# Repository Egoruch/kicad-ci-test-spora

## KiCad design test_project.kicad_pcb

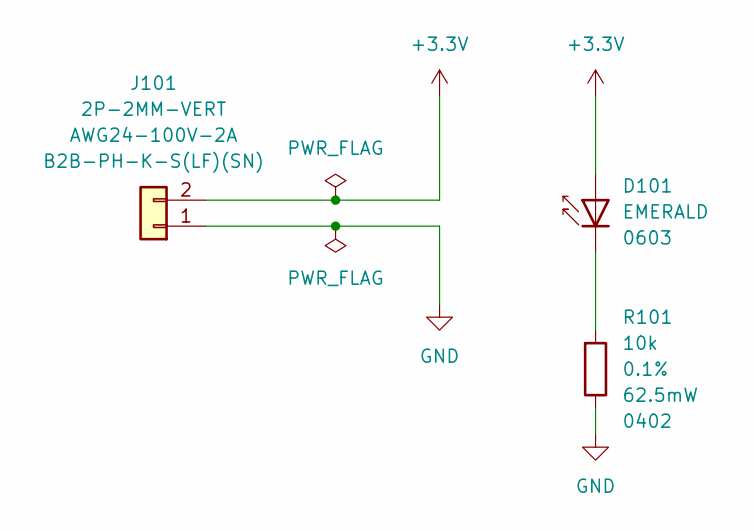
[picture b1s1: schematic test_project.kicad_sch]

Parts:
D101: EMERALD; LED_0603_E_1608Metric; Manufacturer Part Number 19-217/GHC-YR1S2/3T; LCSC Part Number C72043
J101: 2P-2MM-VERT; JST_PH_B2B-PH-K_1x02_P2.00mm_Vertical; Manufacturer Part Number B2B-PH-K-S(LF)(SN); LCSC Part Number C131337
R101: 10k; R_0402_1005Metric; Tolerance 0.1%; Manufacturer Part Number RT0402BRD0710KL; LCSC Part Number C190095

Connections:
+3.3V: D101.2 (A), J101.2
GND: J101.1, R101.2
unnamed: D101.1 (K), R101.1

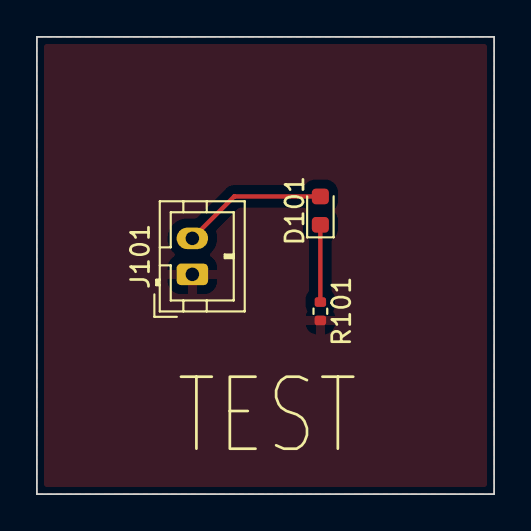
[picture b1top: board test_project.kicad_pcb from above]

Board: 4 copper layers, 25.4 x 25.4 mm, 3 parts (0 on the bottom side), 3 nets.

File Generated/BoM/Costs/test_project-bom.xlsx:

|  | KiBot Bill of Materials
 |  | Schematic: | test_project | Component Groups: | 3
 |  | Variant: | default | Component Count: | 3 (2 SMD/ 1 THT)
 |  | Revision: |  | Fitted Components: | 3 (2 SMD/ 1 THT)
 |  | Date: | 2024-01-10_16-35-41 | Number of PCBs: | 1
 |  | KiCad Version: | 7.0.9-7.0.9~ubuntu23.04.1 | Total Components: | 3
Row | Description | Part | Part Lib | References | Value | Footprint | Footprint Lib | Quantity Per PCB | Build Quantity | Status | Datasheet | Sheetpath | Source BoM | Reference | Package | Manufacturer Part Number | LCSC Part Number | Supplier 1 | Supplier Part Number 1 | Lifecycle | Assembly | Tolerance | Power | Wire | JLCPCB Rotation Offset
1 | Colorless transparence -40℃~+85℃ 520nm~535nm Emerald 120° 110mW 0603 Light Emit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 | 19-217/GHC-YR1S2/3T | Library | D101 | EMERALD | LED_0603_E_1608Metric | LED_SMD | 1 | 1 |  | https://jlcpcb.com/partdetail/EverlightElec-19_217_GHC_YR1S2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 | / | test_project(1) |  | 0603 | 19-217/GHC-YR1S2/3T | C72043 |  |  | ✅ Production
2 | 1x2P PH 1 2mm 2 Brass Straight,P=2mm Wire To Board / Wire To Wire Connector ROHS | B2B-PH-K-S(LF)(SN) | Library | J101 | 2P-2MM-VERT | JST_PH_B2B-PH-K_1x02_P2.00mm_Vertical | Connector_JST | 1 | 1 |  | https://jlcpcb.com/partdetail/Jst_SalesAmerica-B2B_PH_K_S_LF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 | / | test_project(1) |  | Straight,P=2mm | B2B-PH-K-S(LF)(SN) | C131337 |  |  | ✅ Production |  |  |  | AWG24-100V-2A | 180
3 | 62.5mW Thin Film Resistor ±25ppm/℃ ±0.1% 10kΩ 0402 Chip Resistor - Surface Moun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 | RT0402BRD0710KL | Library | R101 | 10k 0.1% 62.5mW | R_0402_1005Metric | Resistor_SMD | 1 | 1 |  | https://jlcpcb.com/partdetail/Yageo-RT0402BRD0710KL/C190095 | / | test_project(1) |  | 0402 | RT0402BRD0710KL | C190095 |  |  | 🔵 Prototype |  | 0.1% | 62.5mW

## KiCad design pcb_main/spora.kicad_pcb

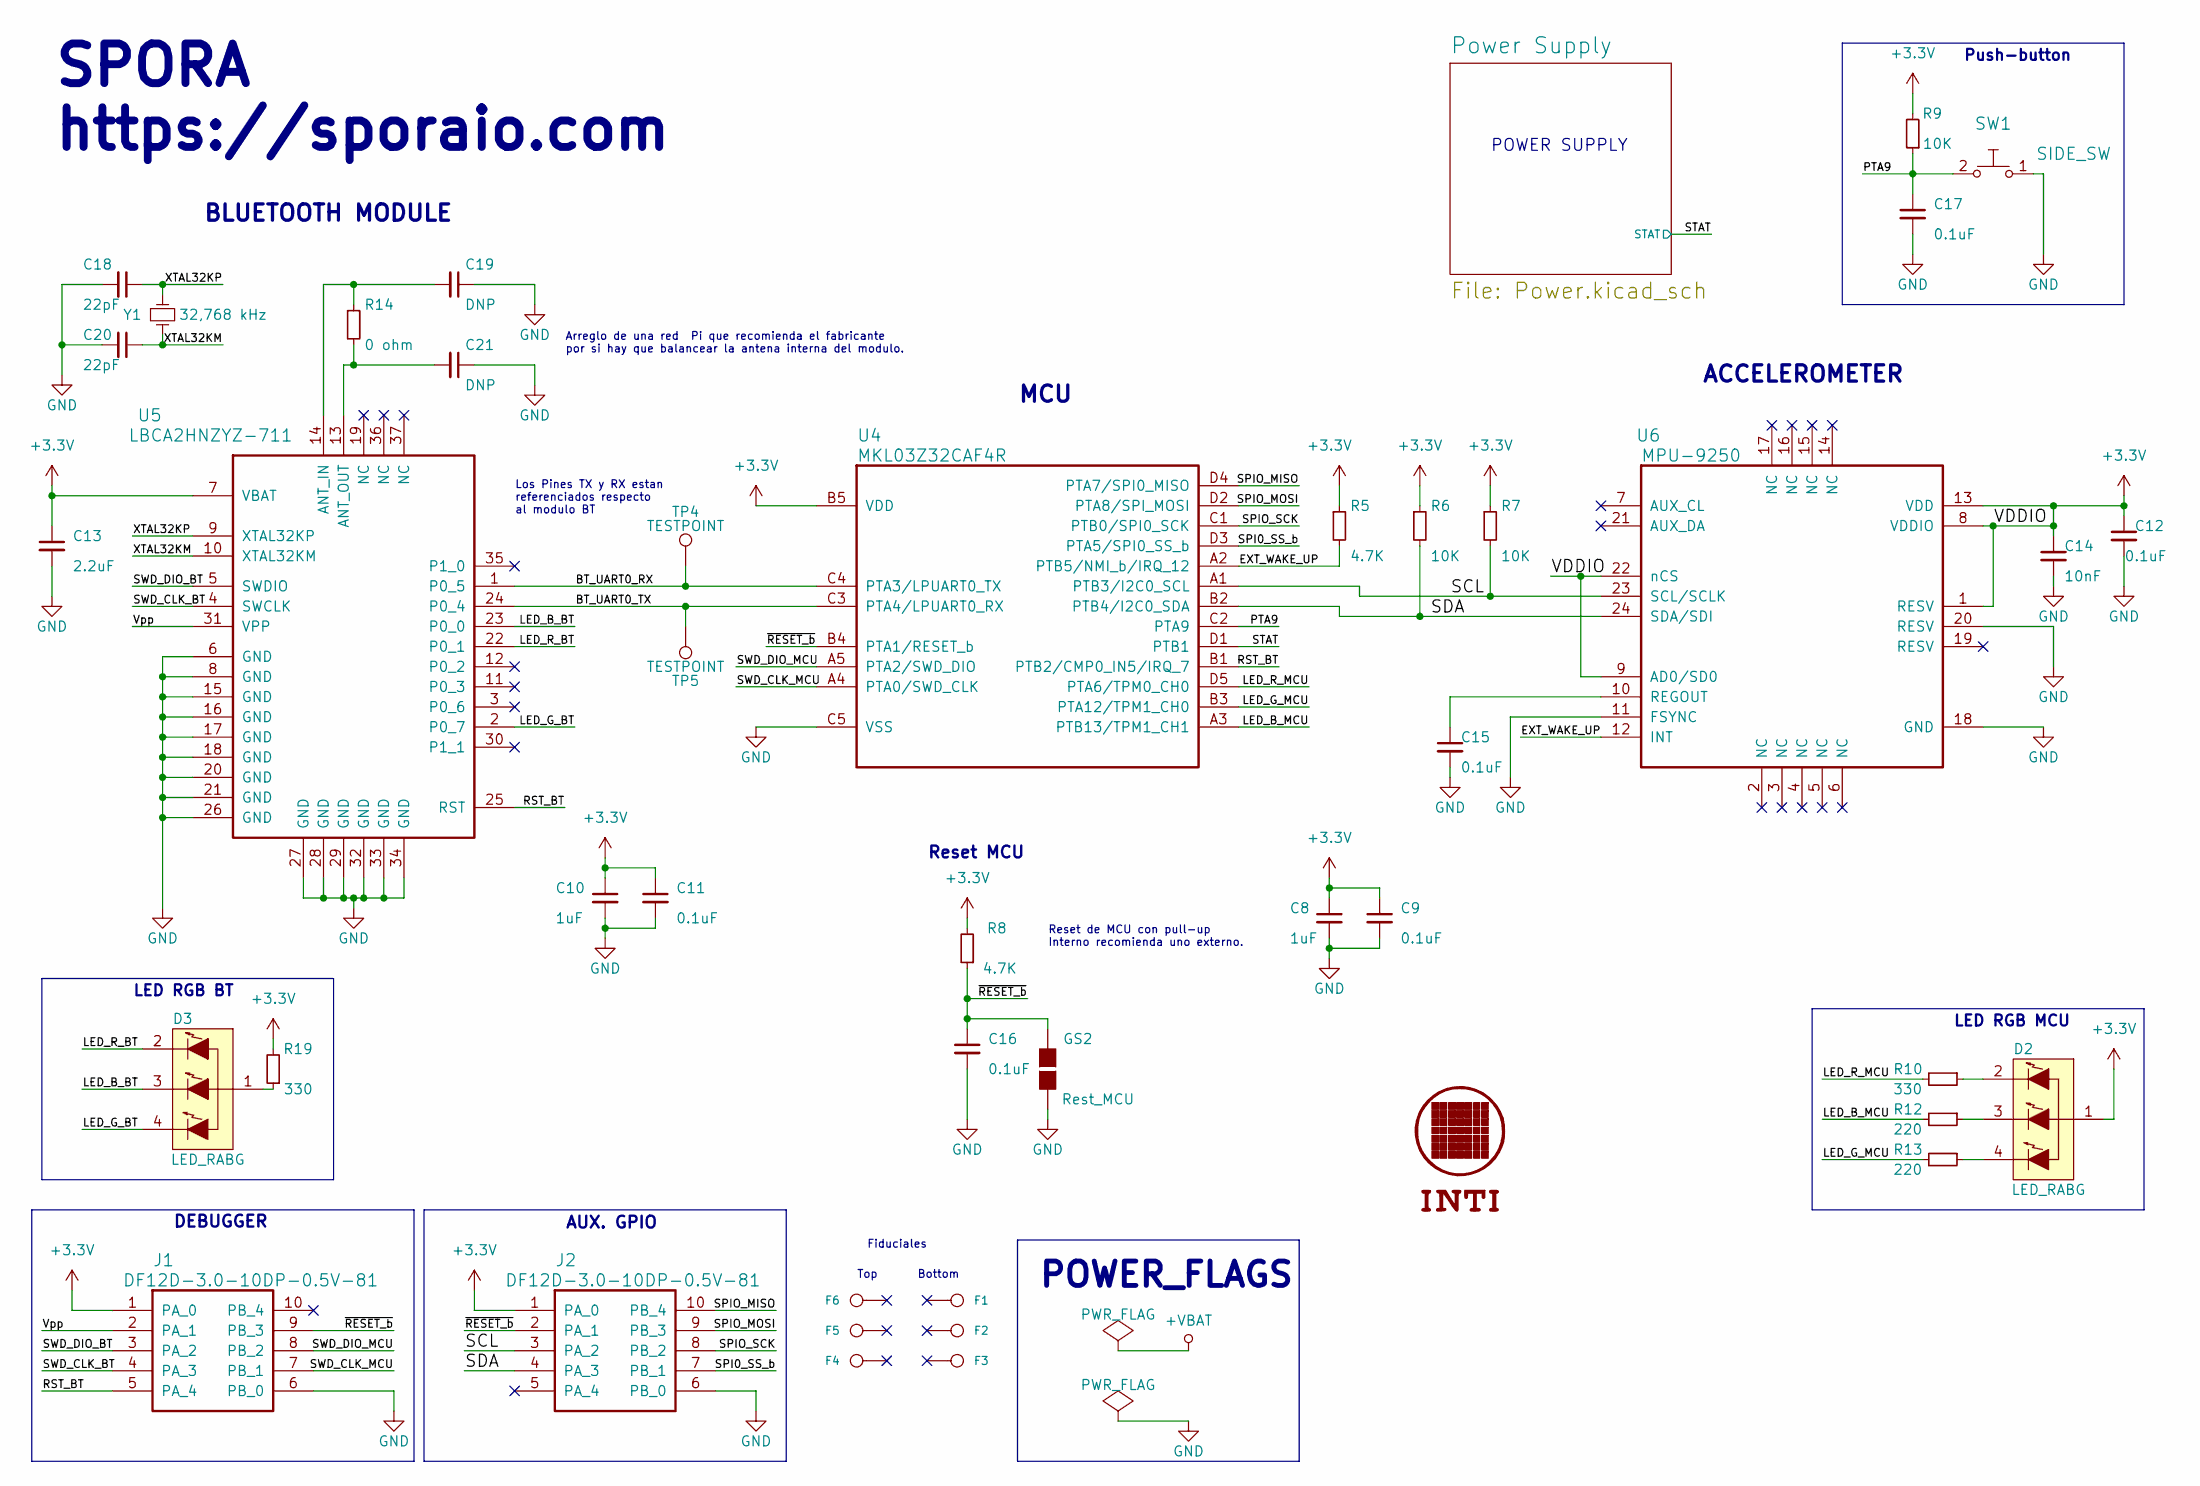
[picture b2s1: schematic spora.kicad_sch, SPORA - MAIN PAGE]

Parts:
C8, C10: 1uF; c_0201; digikey# 1276-6816-1-ND
C9, C11, C12, C15, C16, C17: 0.1uF; c_0201; digikey# 490-5405-1-ND
C13: 2.2uF; c_0201; digikey# 490-13224-1-ND
C14: 10nF; c_0201; digikey# 490-3166-1-ND
C18, C20: 22pF; c_0402; digikey# 732-7427-1-ND
C19, C21: DNP; c_0402
D2, D3: LED_RABG; SML-LX0404SIUPGUSB; digikey# 67-2125-1-ND
F1, F2, F3, F4, F5, F6: CONN_1; FIDUCIAL_65MIL
G1: LOGO_INTI
GS2: Rest_MCU; GS2
J1, J2: DF12D-3.0-10DP-0.5V-81; df12(3.0)-10dp-0.5v; digikey# H11736CT-ND
R5, R8: 4.7K; r_0201; digikey# 311-4.7KNCT-ND
R6, R7, R9: 10K; r_0201; digikey# 311-10KNCT-ND
R10, R19: 330; r_0201; digikey# 311-330NCT-ND
R12, R13: 220; r_0201; digikey# 311-220NCT-ND
R14: 0 ohm; r_0402; digikey# 311-0.0JRTR-ND
SW1: SIDE_SW; B3U_3000PB; digikey# SW1256DKR-ND
TP4, TP5: TESTPOINT
U4: MKL03Z32CAF4R; mouser# 841-MKL03Z32CAF4R; digikey# MKL03Z32CAF4RTR-ND
U5: LBCA2HNZYZ-711; LBCA2A2HNZYZ-711; digikey# 490-10561-1-ND
U6: MPU-9250; digikey# 1428-1019-1-ND
Y1: 32,768 kHz; ABS05-32.768KHZ-9-T; digikey# 535-11897-1-ND

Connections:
+3V3: C8.1, C9.1, C10.1, C11.1, C12.1, C13.1, C14.1, D2.1 (COMMON_ANODE), J1.1 (PA_0), J2.1 (PA_0), R5.1, R6.1, R7.1, R8.2, R9.2, R19.2, U4.B5 (VDD), U5.7 (VBAT), U6.1 (RESV), U6.8 (VDDIO), U6.9 (AD0/SD0), U6.13 (VDD), U6.22 (nCS); also elsewhere on the board
/BT_UART0_RX: TP4.1, U4.C4 (PTA3/LPUART0_TX), U5.1 (P0_5)
/BT_UART0_TX: TP5.1, U4.C3 (PTA4/LPUART0_RX), U5.24 (P0_4)
/EXT_WAKE_UP: R5.2, U4.A2 (PTB5/NMI_b/IRQ_12), U6.12 (INT)
/LED_B_BT: D3.3 (GREEN_CATHODE), U5.23 (P0_0)
/LED_B_MCU: R12.2, U4.A3 (PTB13/TPM1_CH1)
/LED_G_BT: D3.4 (BLUE_CATHODE), U5.2 (P0_7)
/LED_G_MCU: R13.2, U4.B3 (PTA12/TPM1_CH0)
/LED_R_BT: D3.2 (RED_CATHODE), U5.22 (P0_1)
/LED_R_MCU: R10.2, U4.D5 (PTA6/TPM0_CH0)
/PTA9: C17.1, R9.1, SW1.2, U4.C2 (PTA9)
/Power Supply/STAT: U4.D1 (PTB1); also elsewhere on the board
/RST_BT: J1.5 (PA_4), U4.B1 (PTB2/CMP0_IN5/IRQ_7), U5.25 (RST)
/SCL: J2.3 (PA_2), R7.2, U4.A1 (PTB3/I2C0_SCL), U6.23 (SCL/SCLK)
/SDA: J2.4 (PA_3), R6.2, U4.B2 (PTB4/I2C0_SDA), U6.24 (SDA/SDI)
/SPI0_SS_b: J2.7 (PB_1), U4.D3 (PTA5/SPI0_SS_b)
/SPIO_MISO: J2.10 (PB_4), U4.D4 (PTA7/SPI0_MISO)
/SPIO_MOSI: J2.9 (PB_3), U4.D2 (PTA8/SPI_MOSI)
/SPIO_SCK: J2.8 (PB_2), U4.C1 (PTB0/SPI0_SCK)
/SWD_CLK_BT: J1.4 (PA_3), U5.4 (SWCLK)
/SWD_CLK_MCU: J1.7 (PB_1), U4.A4 (PTA0/SWD_CLK)
/SWD_DIO_BT: J1.3 (PA_2), U5.5 (SWDIO)
/SWD_DIO_MCU: J1.8 (PB_2), U4.A5 (PTA2/SWD_DIO)
/Vpp: J1.2 (PA_1), U5.31 (VPP)
/XTAL32KM: C20.1, U5.10 (XTAL32KM), Y1.2
/XTAL32KP: C18.1, U5.9 (XTAL32KP), Y1.1
/~RESET_b: C16.1, GS2.1 (G1), J1.9 (PB_3), J2.2 (PA_1), R8.1, U4.B4 (PTA1/RESET_b)
GND: C8.2, C9.2, C10.2, C11.2, C12.2, C13.2, C14.2, C15.2, C16.2, C17.2, C18.2, C19.1, C20.2, C21.1, GS2.2 (G2), J1.6 (PB_0), J2.6 (PB_0), SW1.1, U4.C5 (VSS), U5.6 (GND), U5.8 (GND), U5.15 (GND), U5.16 (GND), U5.17 (GND), U5.18 (GND), U5.20 (GND), U5.21 (GND), U5.26 (GND), U5.27 (GND), U5.28 (GND), U5.29 (GND), U5.32 (GND), U5.33 (GND), U5.34 (GND), U6.11 (FSYNC), U6.18 (GND), U6.20 (RESV); also elsewhere on the board
unnamed: C15.1, U6.10 (REGOUT)
unnamed: C19.2, R14.1, U5.14 (ANT_IN)
unnamed: C21.2, R14.2, U5.13 (ANT_OUT)
unnamed: D2.2 (RED_CATHODE), R10.1
unnamed: D2.3 (GREEN_CATHODE), R12.1
unnamed: D2.4 (BLUE_CATHODE), R13.1
unnamed: D3.1 (COMMON_ANODE), R19.1

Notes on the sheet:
Fiduciales
Bottom
SPORA https://sporaio.com
POWER_FLAGS
LED RGB MCU
POWER SUPPLY
Reset MCU
Reset de MCU con pull-up Interno recomienda uno externo.
BLUETOOTH MODULE
Arreglo de una red Pi que recomienda el fabricante por si hay que balancear la antena interna del modulo.
ACCELEROMETER
Top
MCU
LED RGB BT
AUX. GPIO
Push-button
DEBUGGER
Los Pines TX y RX estan referenciados respecto al modulo BT

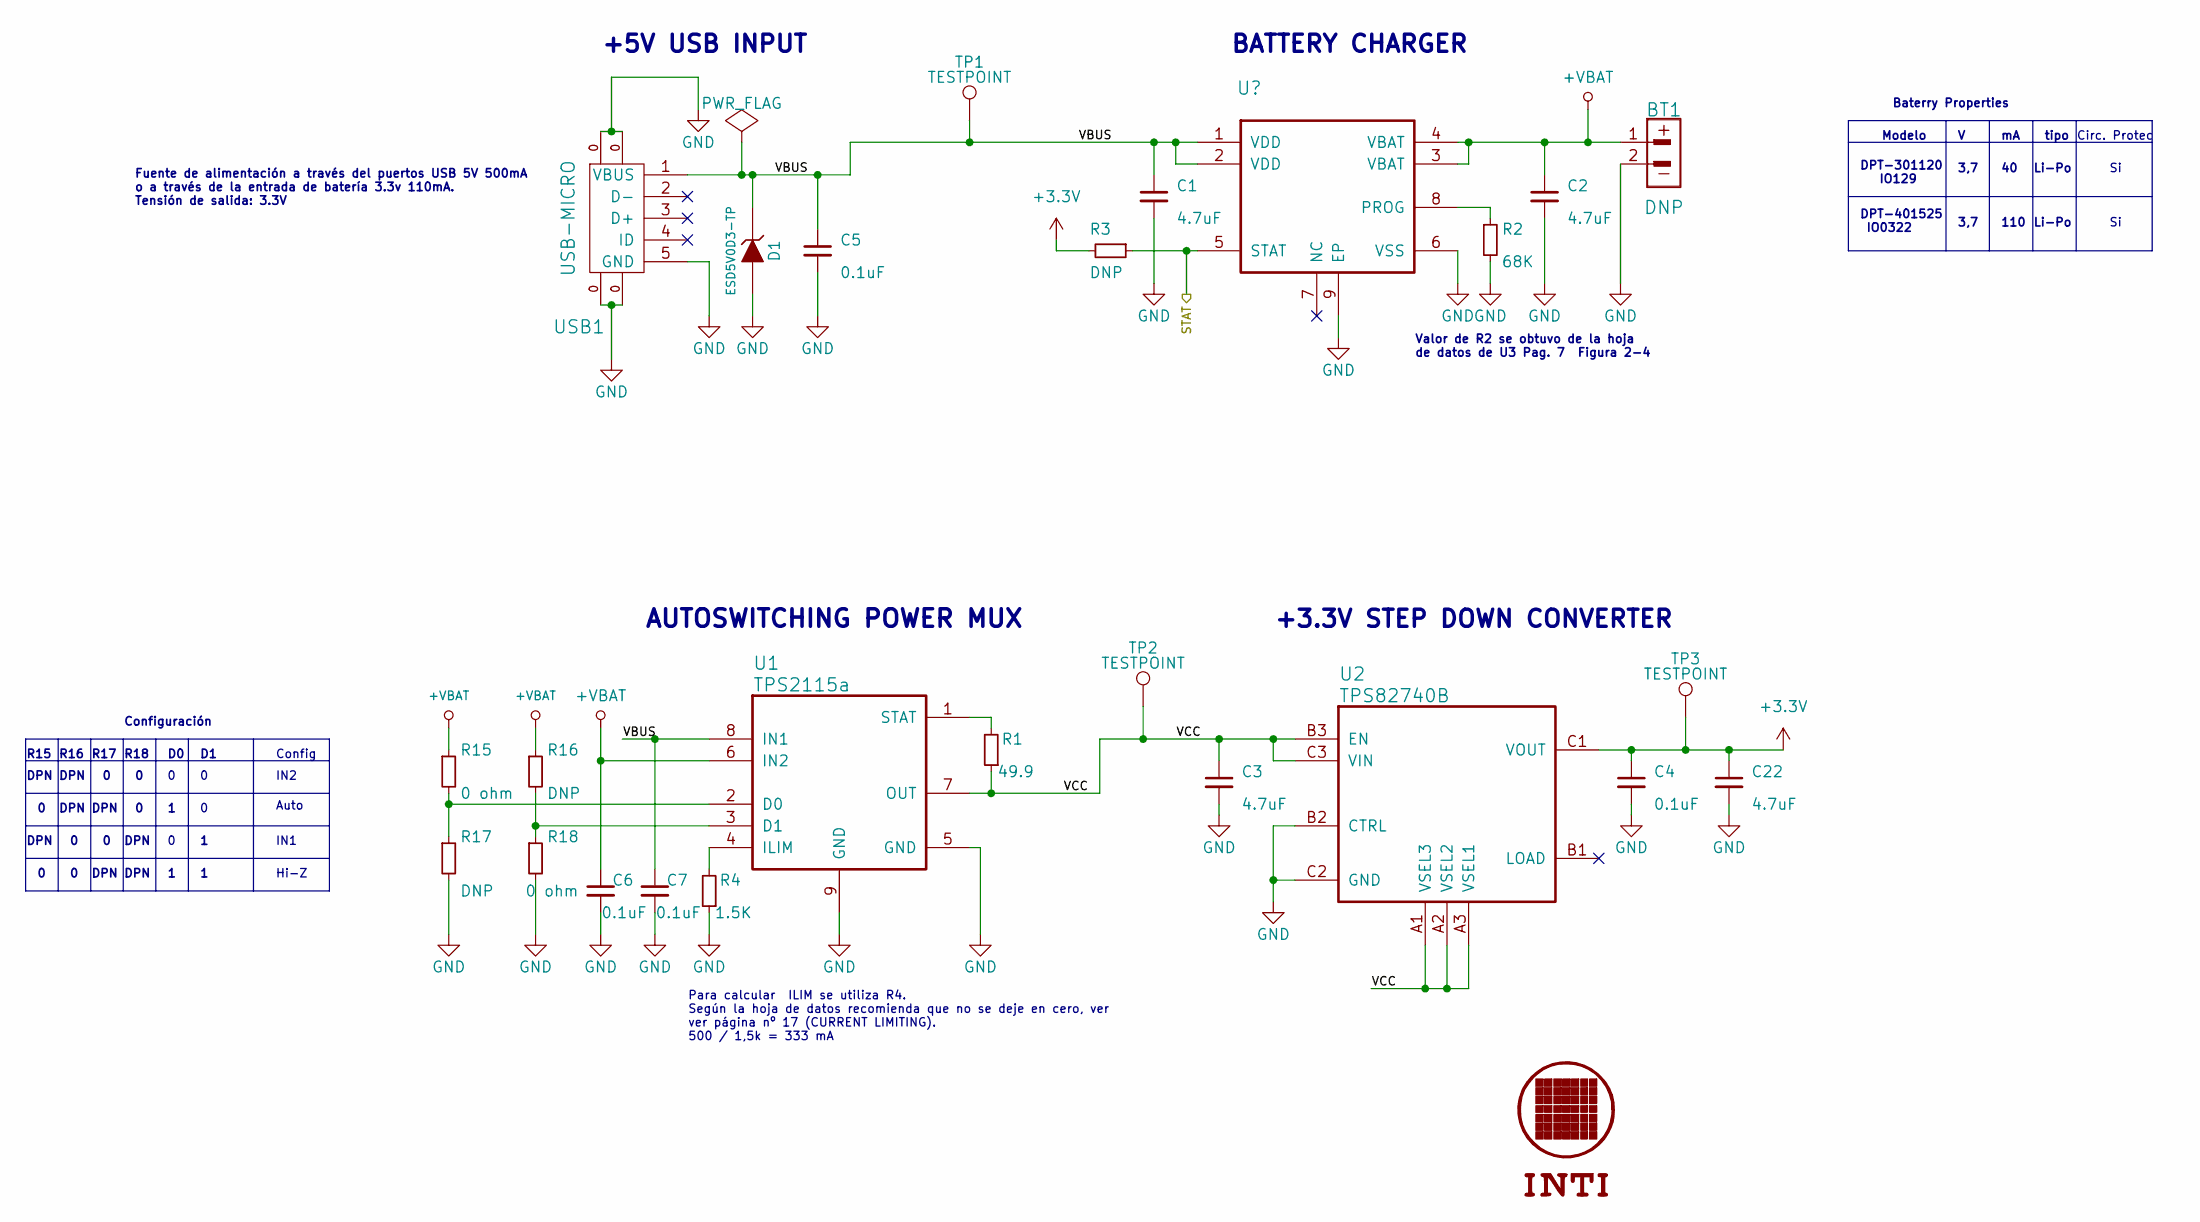
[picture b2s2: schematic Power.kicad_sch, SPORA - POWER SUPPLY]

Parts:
BT1: DNP; BAT_CON
C1, C2, C3, C22: 4.7uF; c_0201; digikey# 490-13230-1-ND
C4, C5, C6, C7: 0.1uF; c_0201; digikey# 490-5405-1-ND
D1: ESD5V0D3-TP; SOD-323; digikey# ESD5V0D3-TPMSCT-ND
G2: LOGO_INTI
R1: 49.9; r_0201; digikey# P49.9ABCT-ND
R2: 68K; r_0201; digikey# P68.0KABCT-ND
R3: DNP; r_0201; digikey# 311-470NCT-ND
R4: 1.5K; r_0201; digikey# 311-1.5KNCT-ND
R15, R18: 0 ohm; r_0402; digikey# 311-0.0JRCT-ND
R16, R17: DNP; r_0402
TP1, TP2, TP3: TESTPOINT
U1: TPS2115a; TPS2115A; digikey# 296-23394-1-ND
U2: TPS82740B; digikey# 296-37973-1-ND
USB1: USB-MICRO; conn_usb_B_micro_smd; digikey# H125279CT-ND

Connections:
+3V3: C4.1, C22.1, R3.2, TP3.1, U2.C1 (VOUT); also elsewhere on the board
+VBAT: BT1.1, C2.1, C6.1, R15.1, R16.1, U1.6 (IN2); also elsewhere on the board
/Power Supply/STAT: R3.1; also elsewhere on the board
/Power Supply/VBUS: C1.1, C5.1, C7.1, D1.1 (K), TP1.1, U1.8 (IN1), USB1.1 (VBUS); also elsewhere on the board
/Power Supply/VCC: C3.1, R1.1, TP2.1, U1.7 (OUT), U2.A1 (VSEL3), U2.A2 (VSEL2), U2.A3 (VSEL1), U2.B3 (EN), U2.C3 (VIN)
GND: BT1.2, C1.2, C2.2, C3.2, C4.2, C5.2, C6.2, C7.2, C22.2, D1.2 (A), R2.2, R4.1, R17.2, R18.2, U1.5 (GND), U1.9 (GND), U2.B2 (CTRL), U2.C2 (GND), USB1.0, USB1.5 (GND); also elsewhere on the board
unnamed: R1.2, U1.1 (STAT)
unnamed 41: R2.1; also elsewhere on the board
unnamed: R4.2, U1.4 (ILIM)
unnamed: R15.2, R17.1, U1.2 (D0)
unnamed: R16.2, R18.1, U1.3 (D1)

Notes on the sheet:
DPT-301120 IO129
DPN
Baterry Properties
Valor de R2 se obtuvo de la hoja de datos de U3 Pag. 7 Figura 2-4
3,7
BATTERY CHARGER
Para calcular ILIM se utiliza R4. Según la hoja de datos recomienda que no se deje en cero, ver ver página nº 17 (CURRENT LIMITING). 500 / 1,5k = 333 mA
AUTOSWITCHING POWER MUX
Auto
DPT-401525 IO0322
IN1
R18
Li-Po
R17
Fuente de alimentación a través del puertos USB 5V 500mA o a través de la entrada de batería 3.3v 110mA. Tensión de salida: 3.3V
+3.3V STEP DOWN CONVERTER
110
Config
Hi-Z
+5V USB INPUT
R15
tipo
R16
Modelo
IN2
Configuración
Circ. Protec

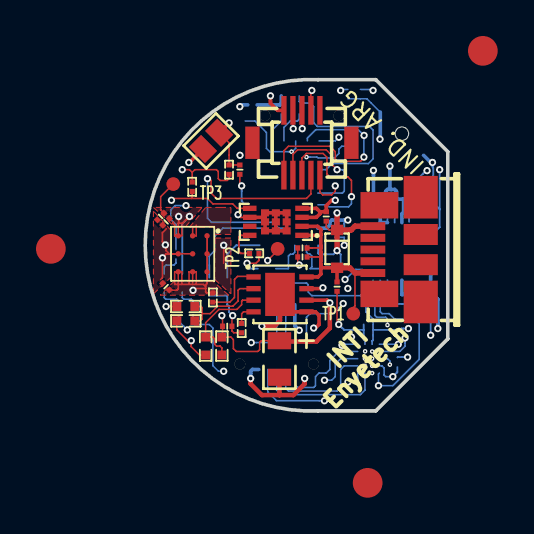
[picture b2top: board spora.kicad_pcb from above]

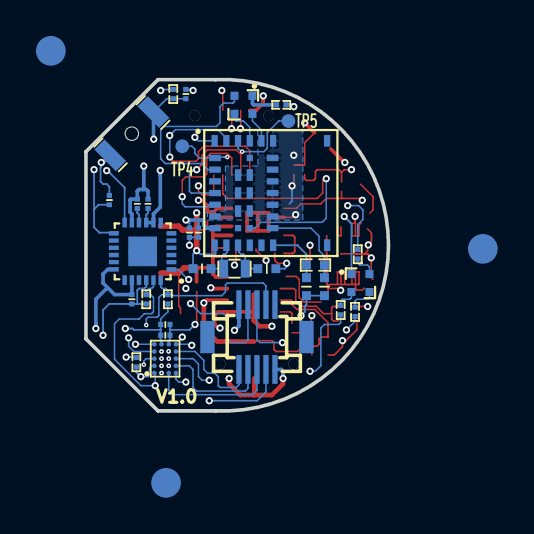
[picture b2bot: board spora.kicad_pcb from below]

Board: 6 copper layers, 16.8 x 18.4 mm, 67 parts (35 on the bottom side), 43 nets.

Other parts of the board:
U3: MCP73831; MCP73821

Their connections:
+VBAT: U3.3, U3.4; also elsewhere on the board
/Power Supply/STAT: U3.5; also elsewhere on the board
/Power Supply/VBUS: U3.1, U3.2; also elsewhere on the board
GND: U3.6, U3.9; also elsewhere on the board
unnamed 41: U3.8; also elsewhere on the board

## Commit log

2024-01-10 test: kicad6
2024-01-10 test; sch chnage
2024-01-10 test: test project
2024-01-10 test: without deploy pages
2024-01-10 test: com&push files
2024-01-10 test: lib path
2024-01-10 test: again
2024-01-10 test: try to delete library file wihout sudo
2024-01-10 test: push generated files to repo
2024-01-10 test: commit na push Generated
2024-01-10 chore: autopublish 2024-01-10T16:40:12Z

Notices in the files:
pcb_main/Power.kicad_sch:
BSD License.  See LICENSE.txt file
